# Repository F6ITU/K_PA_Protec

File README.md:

# K_PA_Protec

OpenHPSDR P.A. Protection board by LA2NI (Munin 400)

This protection board is part of a set consisting of a 400 W LD-Mos based RF power amplifier (Munin 400), 
a medium power (600 or 1500 W) Zolotarev low pass filter, an Automatic Antenna Tuner (ATU) nickname « Aries » 
and a 4 port antenna switch.

All these developments are the work and intellectual property of Kjell Karsten LA2NI and Laurence Barker G8NJJ.

This original work can be downloaded from 

https://github.com/LA2NI/

https://github.com/laurencebarker

The protection board ensures the physical measurements of the amplifier (VSWR, Power, Voltage, Current) and the shutdown of this amplifier in case of issues detected 
either by Aries (too high VSWR) or by any other sensor located on the amplifier itself or the ATU(temperature, voltage, current). It is used between Aries and Munin 400. 

For more information, please refer to the Aries documentation (in the G8NJJ github repository)

This board was originally developed in September 2021 by Kjell LA2NI , with UltiBoard EDA. This repository is a « bug for bug » clone of the original Protection Board using the Opensource 
Kicad EDA. All these KiCad files are, consequently, the intellectual property of Kjell LA2NI.

This portage (convertion/translation) is placed under the CERN Open source/ Open hardware Licence.

Kicad is an Opensource EDA software maintained by the European Reseach Center CERN (Conseil européen pour la recherche nucléaire)

The original work is protected by the TAPR Open Hardware licence

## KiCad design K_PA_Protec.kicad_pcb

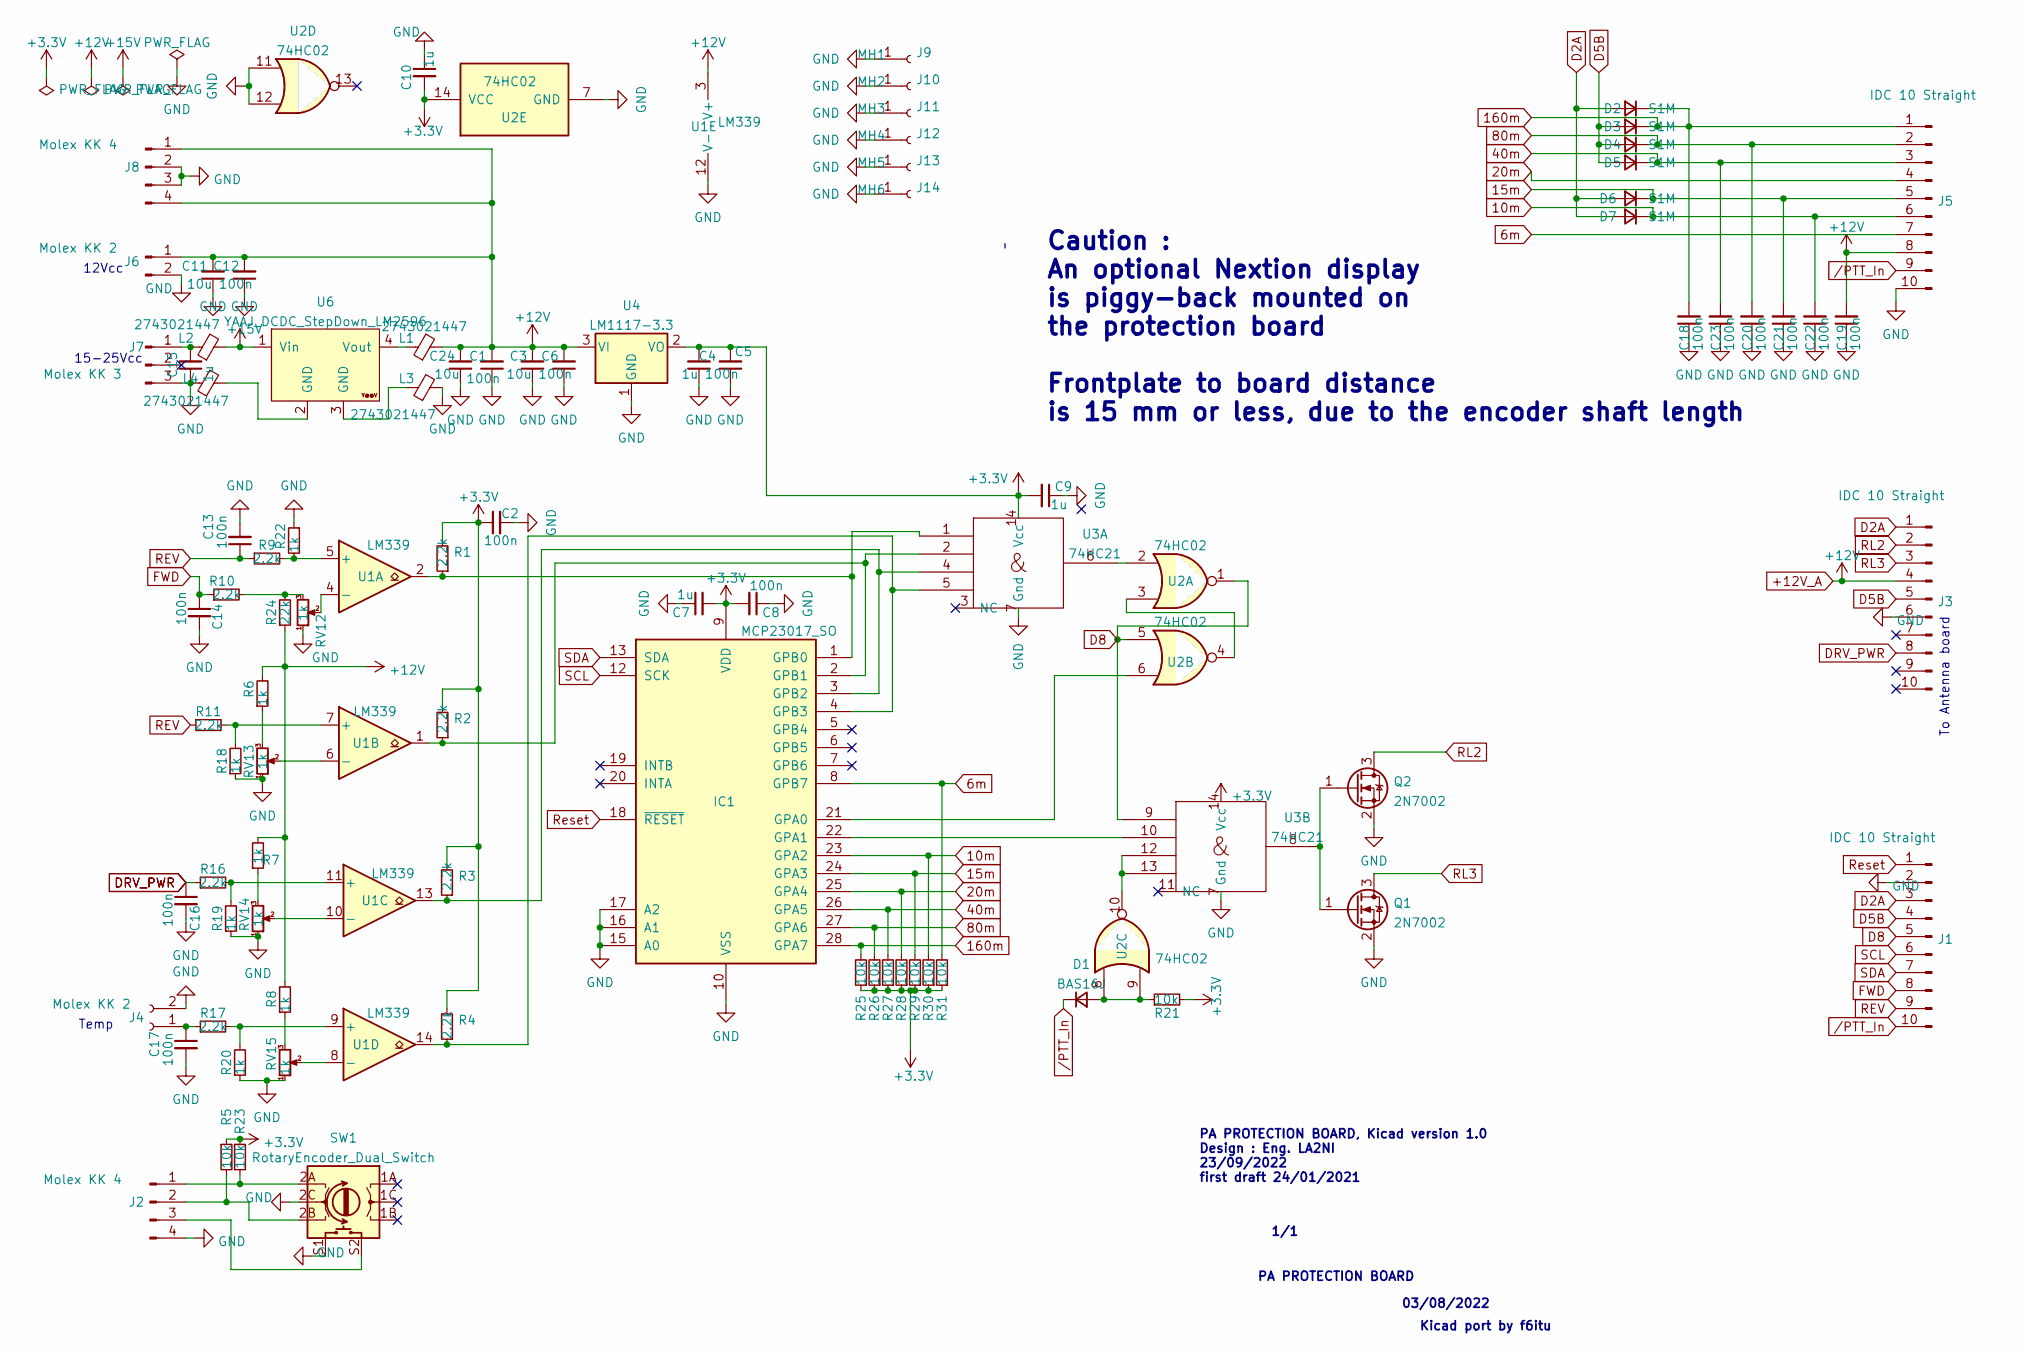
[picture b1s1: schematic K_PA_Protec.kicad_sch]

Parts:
C1, C2, C5, C6, C8, C12, C13, C14, C16, C17, C18, C19, C20, C21, C22, C23: 100n; C_0805_2012Metric_Pad1.18x1.45mm_HandSolder
C3, C11, C24: 10u; C_0805_2012Metric_Pad1.18x1.45mm_HandSolder
C4, C7, C9, C10, C15: 1u; C_0805_2012Metric_Pad1.18x1.45mm_HandSolder
D1: BAS16J; D_SOD-323
D2, D3, D4, D5, D6, D7: S1M; D_SMA_Handsoldering
IC1: MCP23017_SO; SOIC-28W_7.5x17.9mm_P1.27mm
J1, J3, J5: IDC 10 Straight; IDC-Header_2x05_P2.54mm_Vertical
J2, J8: Molex KK 4; Molex_KK-254_AE-6410-04A_1x04_P2.54mm_Vertical
J4, J6: Molex KK 2; Molex_KK-254_AE-6410-02A_1x02_P2.54mm_Vertical
J7: Molex KK 3; Molex_KK-254_AE-6410-03A_1x03_P2.54mm_Vertical
J9: MH1; MountingHole_3.2mm_M3_Pad_Via
J10: MH2; MountingHole_3.2mm_M3_Pad_Via
J11: MH3; MountingHole_3.2mm_M3_Pad_Via
J12: MH4; MountingHole_3.2mm_M3_Pad_Via
J13: MH5; MountingHole_3.2mm_M3_Pad_Via
J14: MH6; MountingHole_3.2mm_M3_Pad_Via
L1, L2, L3, L4: 2743021447; Fair-Rite_2743021447
Q1, Q2: 2N7002; SOT-23
R1, R2, R3, R4, R9, R10, R11, R16, R17: 2.2k; R_0805_2012Metric_Pad1.20x1.40mm_HandSolder
R5, R21, R23, R25, R26, R27, R28, R29, R30, R31: 10k; R_0805_2012Metric_Pad1.20x1.40mm_HandSolder
R6, R7, R8, R18, R19, R20, R22: 1k; R_0805_2012Metric_Pad1.20x1.40mm_HandSolder
R24: 22k; R_0805_2012Metric_Pad1.20x1.40mm_HandSolder
RV12, RV13, RV14, RV15: 1k; Potentiometer_Bourns_TC33X_Vertical
SW1: RotaryEncoder_Dual_Switch; RotaryEncoder_Dual_Alps_EC11E-Switch_Vertical_H20mm
U1: LM339; SOIC-14_3.9x8.7mm_P1.27mm
U2: 74HC02; SOIC-14_3.9x8.7mm_P1.27mm
U3: 74HC21; SOIC-14_3.9x8.7mm_P1.27mm
U4: LM1117-3.3; SOT-223-3_TabPin2
U6: YAAJ_DCDC_StepDown_LM2596

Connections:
6m: IC1.8 (GPB7), J5.7, R31.2
10m: C22.2, D7.1 (K), IC1.23 (GPA2), J5.6, R30.2
15m: C21.2, D6.1 (K), IC1.24 (GPA3), J5.5, R29.2
20m: IC1.25 (GPA4), J5.4, R28.2
40m: C23.2, D5.1 (K), IC1.26 (GPA5), J5.3, R27.2
80m: C20.2, D4.1 (K), IC1.27 (GPA6), J5.2, R26.2
160m: C18.2, D2.1 (K), D3.1 (K), IC1.28 (GPA7), J5.1, R25.2
+3V3: C2.1, C4.2, C5.2, C7.2, C8.2, C9.2, C10.2, IC1.9 (VDD), R1.2, R2.2, R3.2, R4.2, R5.1, R21.2, R23.1, R25.1, R26.1, R27.1, R28.1, R29.1, R30.1, R31.1, U2.14 (VCC), U3.14 (Vcc), U4.2 (VO)
+12V_A: C1.2, C3.2, C6.2, C11.2, C12.2, C19.2, C24.2, J3.4, J5.8, J6.1, J8.1, J8.4, L1.2, R6.2, R7.2, R8.2, R24.1, U1.3 (V+), U4.3 (VI)
+15V: L2.2, U6.1 (Vin)
D2A: D2.2 (A), D6.2 (A), D7.2 (A), J1.3, J3.1
D5B: D3.2 (A), D4.2 (A), D5.2 (A), J1.4, J3.5
D8: J1.5, U2.1, U2.5, U3.9
DRV_PWR: C16.1, J3.8, R16.1
FWD: C14.1, J1.8, R10.1
unnamed: C17.1, J4.1, R17.1
unnamed: D1.2 (A), R21.1, U2.8, U2.9
unnamed: IC1.1 (GPB0), R1.1, U1.2, U3.1
unnamed: IC1.2 (GPB1), R2.1, U1.1, U3.2
unnamed: IC1.3 (GPB2), R3.1, U1.13, U3.4
unnamed: IC1.4 (GPB3), R4.1, U1.14, U3.5
unnamed: IC1.21 (GPA0), U2.6
unnamed: IC1.22 (GPA1), U3.10
unnamed: J2.1, R23.2, SW1.2A
unnamed: J2.2, R5.2, SW1.2B
unnamed: J2.3, SW1.S2
unnamed: L1.1, U6.4 (Vout)
unnamed: L3.1, U6.3 (GND)
unnamed: L4.2, U6.2 (GND)
unnamed: Q1.1 (G), Q2.1 (G), U3.8
unnamed: R6.1, RV13.3
unnamed: R7.1, RV14.3
unnamed: R8.1, RV15.3
unnamed: R10.2, R24.2, RV12.3
unnamed: R11.2, R18.2, U1.7 (+)
unnamed: R16.2, R19.2, U1.11 (+)
unnamed: R17.2, R20.2, U1.9 (+)
unnamed: R9.2, R22.2, U1.5 (+)
unnamed: RV12.2, U1.4 (-)
unnamed: RV13.2, U1.6 (-)
unnamed: RV14.2, U1.10 (-)
unnamed: RV15.2, U1.8 (-)
unnamed: U2.2, U3.6
unnamed: U2.3, U2.4
unnamed: U2.10, U3.12, U3.13
REV: C13.1, J1.9, R9.1, R11.1
RL2: J3.2, Q2.3 (D)
RL3: J3.3, Q1.3 (D)
Reset: IC1.18 (~RESET), J1.1
SCL: IC1.12 (SCK), J1.6
SDA: IC1.13 (SDA), J1.7
/PTT_In: D1.1 (K), J1.10, J5.9

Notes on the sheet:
12Vcc
03/08/2022
PA PROTECTION BOARD, Kicad version 1.0 Design : Eng. LA2NI 23/09/2022 first draft 24/01/2021
Temp
PA PROTECTION BOARD
1/1
Caution : An optional Nextion display is piggy-back mounted on the protection board Frontplate to board distance is 15 mm or less, due to the encoder shaft length
15-25Vcc
Kicad port by f6itu
To Antenna board

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
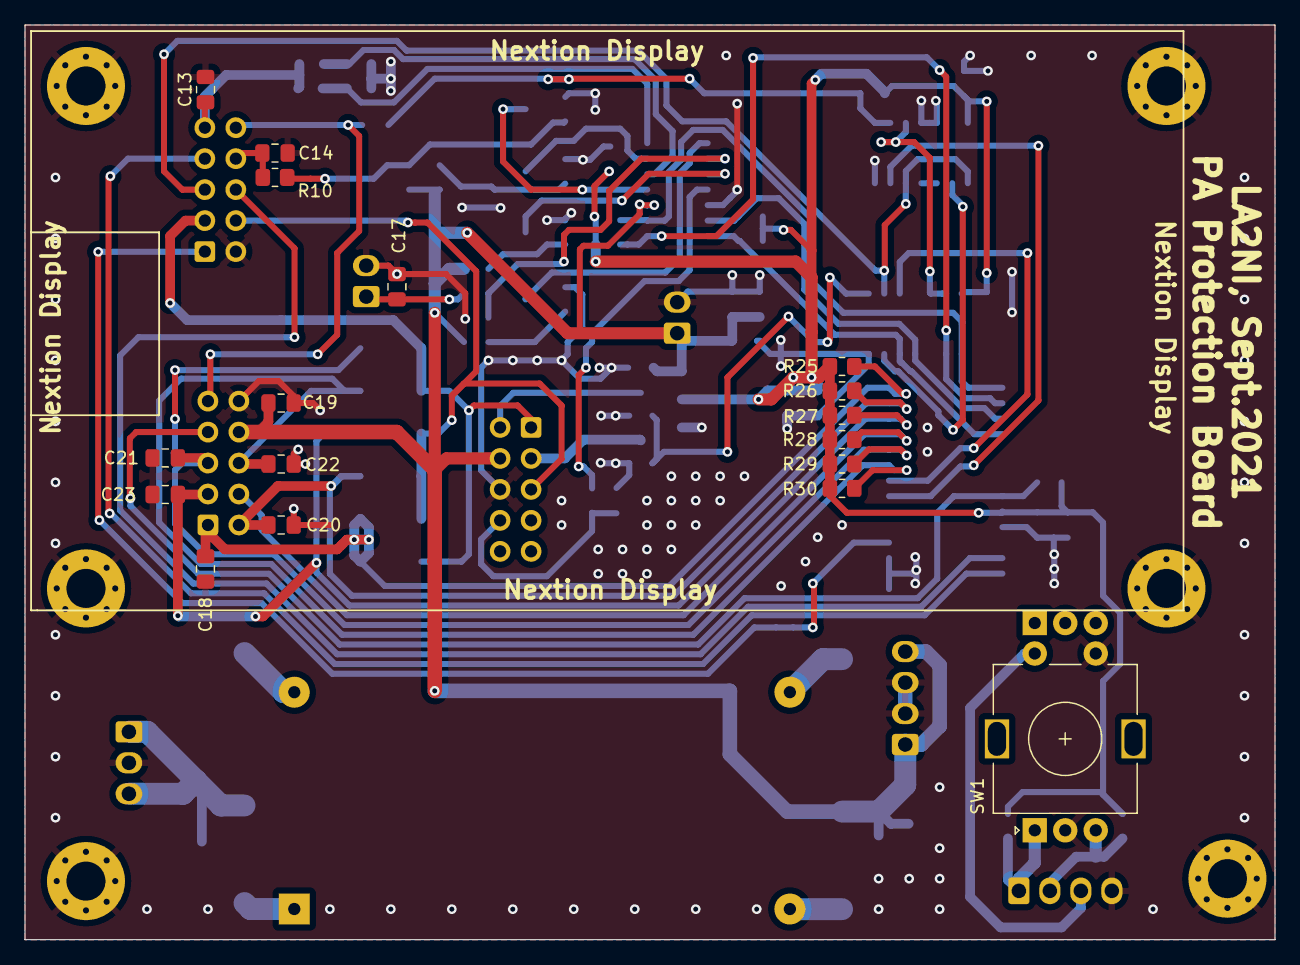
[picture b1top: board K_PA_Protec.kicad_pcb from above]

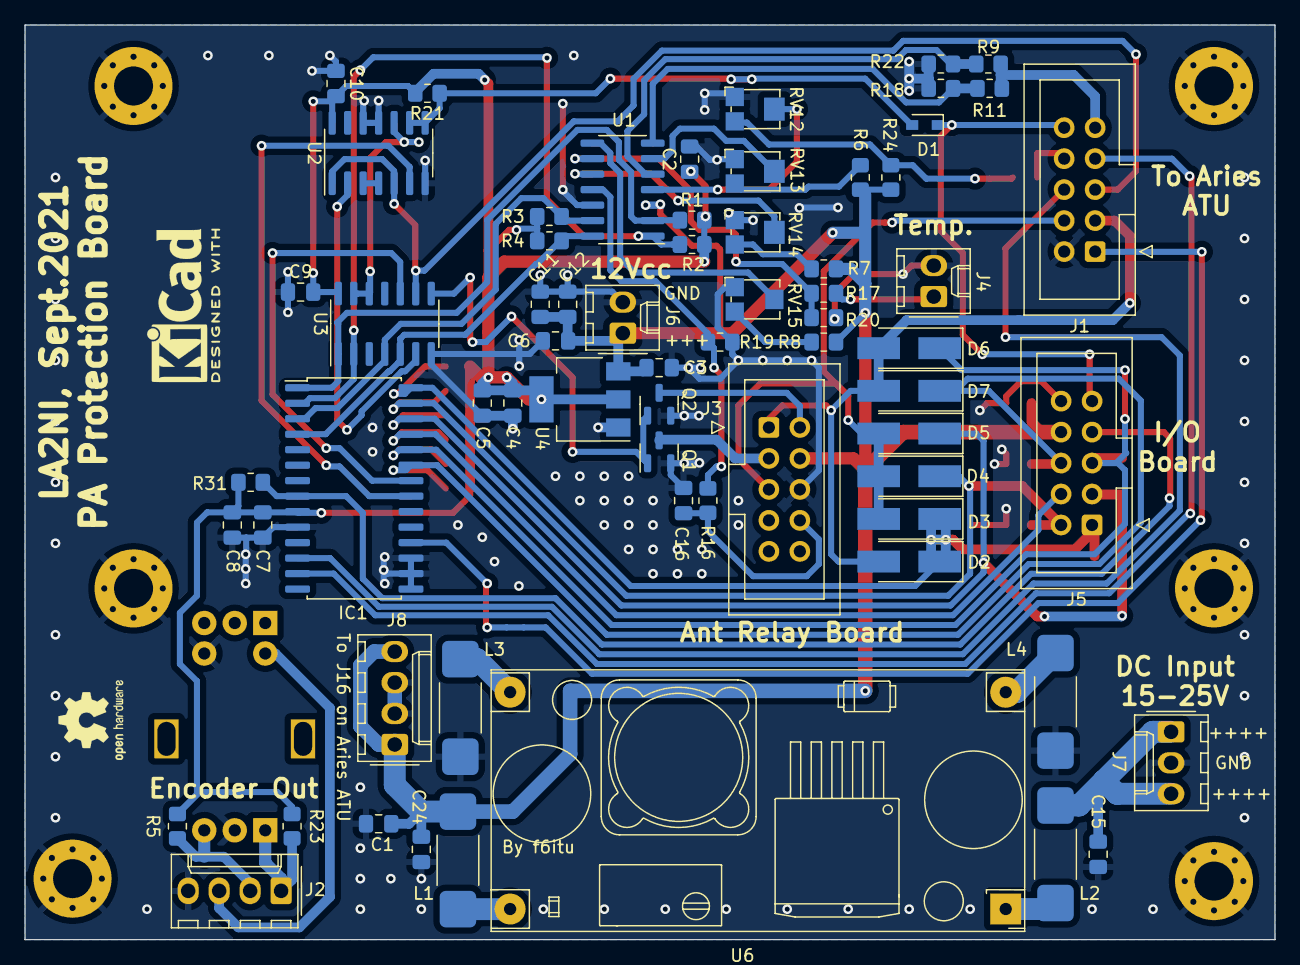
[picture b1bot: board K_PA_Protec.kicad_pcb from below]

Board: 2 copper layers, 102.5 x 75.0 mm, 89 parts (66 on the bottom side), 54 nets.

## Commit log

2022-08-06 first release of the port, placement, no routing
2022-08-06 minor Readme.md modifications
2022-08-06 routing, first stage
2022-08-08 routing completed, some minor changes expected
2022-08-08 some cleaning
2022-08-08 readme picture added
2022-08-08 small layout mods
2022-08-08 silkscreen cleanup, small routing mods
2022-08-08 Last Readme update, new board picture
2022-08-08 ibom added
2022-08-15 nextion mounting holes fixed, last release before proto
2022-08-15 temporary folders deleted
2023-05-10 minor changes in the README file
2024-11-03 Kicad 8.x file format
2024-11-03 Gerber files November 3rd 2024
